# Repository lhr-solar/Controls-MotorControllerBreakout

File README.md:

TODO: update readme for v2.1: added 2 fan connectors, raised TPS2121 current limit & fuse rating

# Controls-MotorControllerBreakout
Author: Ravi Shah  

This Power and CAN interface board for the Prohelion WaveSculptor 22 Motor Controller allows for easier debugging by switching between controls and external power sources and providing a plug-and-play CANdapter interface.  

## BOM
IBOM: BOM/ibom.html (download and view in browser)  
Mouser Cart: https://www.mouser.com/ProjectManager/ProjectDetail.aspx?AccessID=de9c48e362

## Connectors
| # | Name | Type | Ideal Voltage |
| - | - | - | - |
| J1  | MC CAN 1 | Micro-Fit_3.0_43045-0612_2x03_P3.00mm_Vertical Female | +12V |
| J2  | MC CAN 2 | Micro-Fit_3.0_43650-0215_1x02_P3.00mm_Vertical Female | N/A |
| J3  | CTRLS | Micro-Fit_3.0_43045-0612_2x03_P3.00mm_Vertical Female | +12V |
| J4  | EXT PWR | Micro-Fit_3.0_43650-0215_1x02_P3.00mm_Vertical Female | +12V |
| J5  | CANDAPTER | AMPHENOL_L77SDE09SA4CH3R Female | N/A |

## 3D Model

## PCB

## Schematic
### Root

### Power Distribution

### Power Protection

### LEDs

## Application Note
Controls Leader should always be connected to "CTRLS" with the standard CAN+PWR pinout. The motor controller should always be connected to MC CAN 1 and MC CAN 2. To connect external 12V power, the "EXT EN" jumper must be closed. This jumper can be left closed to allow the power muxing IC to choose a source (prioritizing controls), or it can be left open to ignore the external source. In case of a defective IC, the "MNL" jumper can be closed to permanently connect Controls to the output +12V. Otherwise, the "MNL" jumper should be left open.  

+12v is protected by rectifier diodes and fused on both Controls Leader and this board.  

If using a CANdapter for debugging, the "CAN TERM" jumper must be opened. Otherwise, it should be closed, since this board acts as the terminating end for MotorCAN.

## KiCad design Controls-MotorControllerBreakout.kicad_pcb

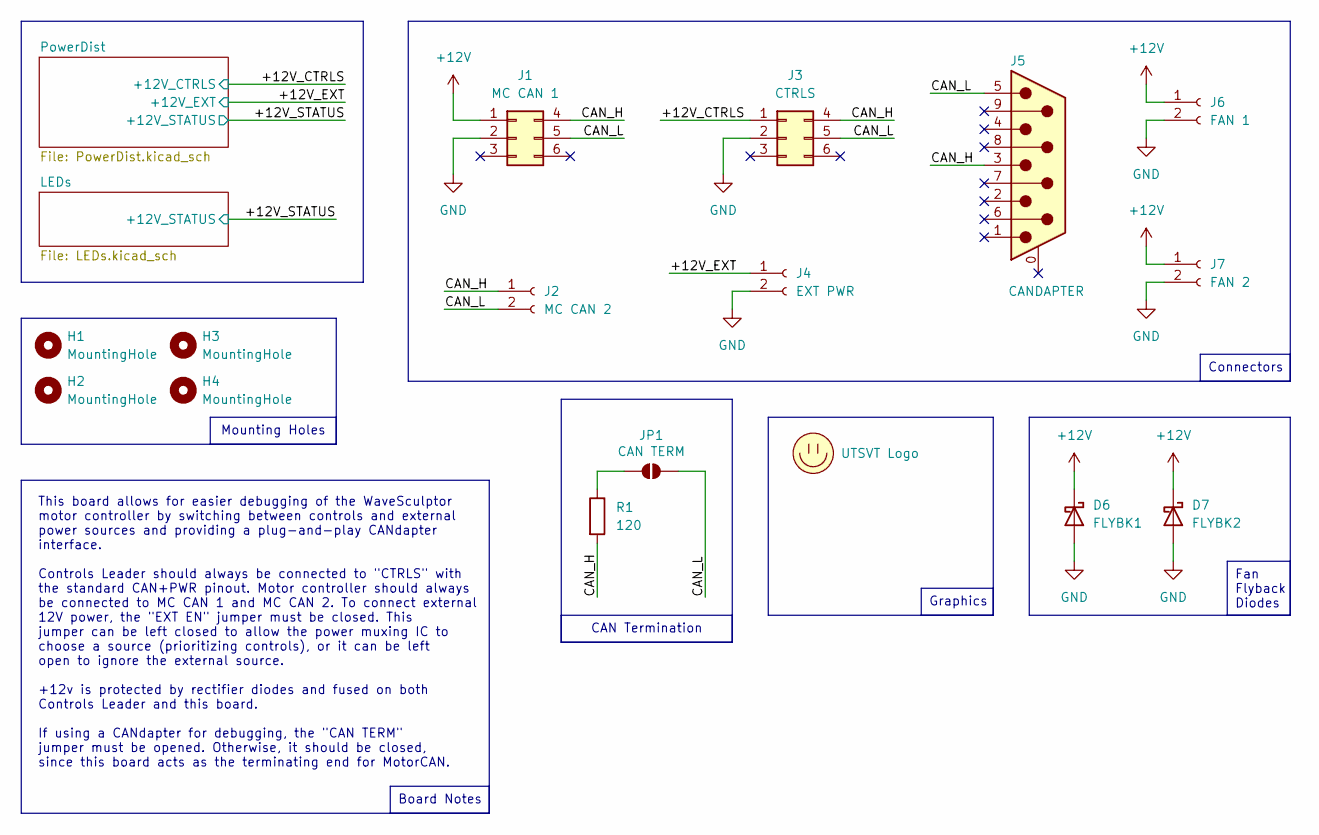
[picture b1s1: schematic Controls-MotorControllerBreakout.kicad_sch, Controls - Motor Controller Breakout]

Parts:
D6: FLYBK1; DO-221AC
D7: FLYBK2; DO-221AC
H1, H2, H3, H4: MountingHole; MountingHole_3mm
J1: MC CAN 1; Molex_Micro-Fit_3.0_43045-0612_2x03_P3.00mm_Vertical
J2: MC CAN 2; Molex_Micro-Fit_3.0_43650-0215_1x02_P3.00mm_Vertical
J3: CTRLS; Molex_Micro-Fit_3.0_43045-0612_2x03_P3.00mm_Vertical
J4: EXT PWR; Molex_Micro-Fit_3.0_43650-0215_1x02_P3.00mm_Vertical
J5: CANDAPTER; AMPHENOL_L77SDE09SA4CH3R
J6: FAN 1; Molex_Micro-Fit_3.0_43650-0215_1x02_P3.00mm_Vertical
J7: FAN 2; Molex_Micro-Fit_3.0_43650-0215_1x02_P3.00mm_Vertical
JP1: CAN TERM; SolderJumper-2_P1.3mm_Open_RoundedPad1.0x1.5mm
LOGO1: UTSVT Logo; UTSVT_Logo_Symbol
R1: 120; R_0805_2012Metric

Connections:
+12V: D6.1 (K), D7.1 (K), J1.1, J6.1, J7.1; also elsewhere on the board
/+12V_CTRLS: J3.1; also elsewhere on the board
/+12V_EXT: J4.1; also elsewhere on the board
/CAN_H: J1.4, J2.1, J3.4, J5.3, R1.2
/CAN_L: J1.5, J2.2, J3.5, J5.5, JP1.2 (B)
GND: D6.2 (A), D7.2 (A), J1.2, J3.2, J4.2, J6.2, J7.2; also elsewhere on the board
unnamed: JP1.1 (A), R1.1

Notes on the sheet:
Graphics
Board Notes
Fan Flyback Diodes
Mounting Holes
Connectors
CAN Termination
This board allows for easier debugging of the WaveSculptor motor controller by switching between controls and external power sources and providing a plug-and-play CANdapter interface. Controls Leader should always be connected to "CTRLS" with the standard CAN+PWR pinout. Motor controller should alw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

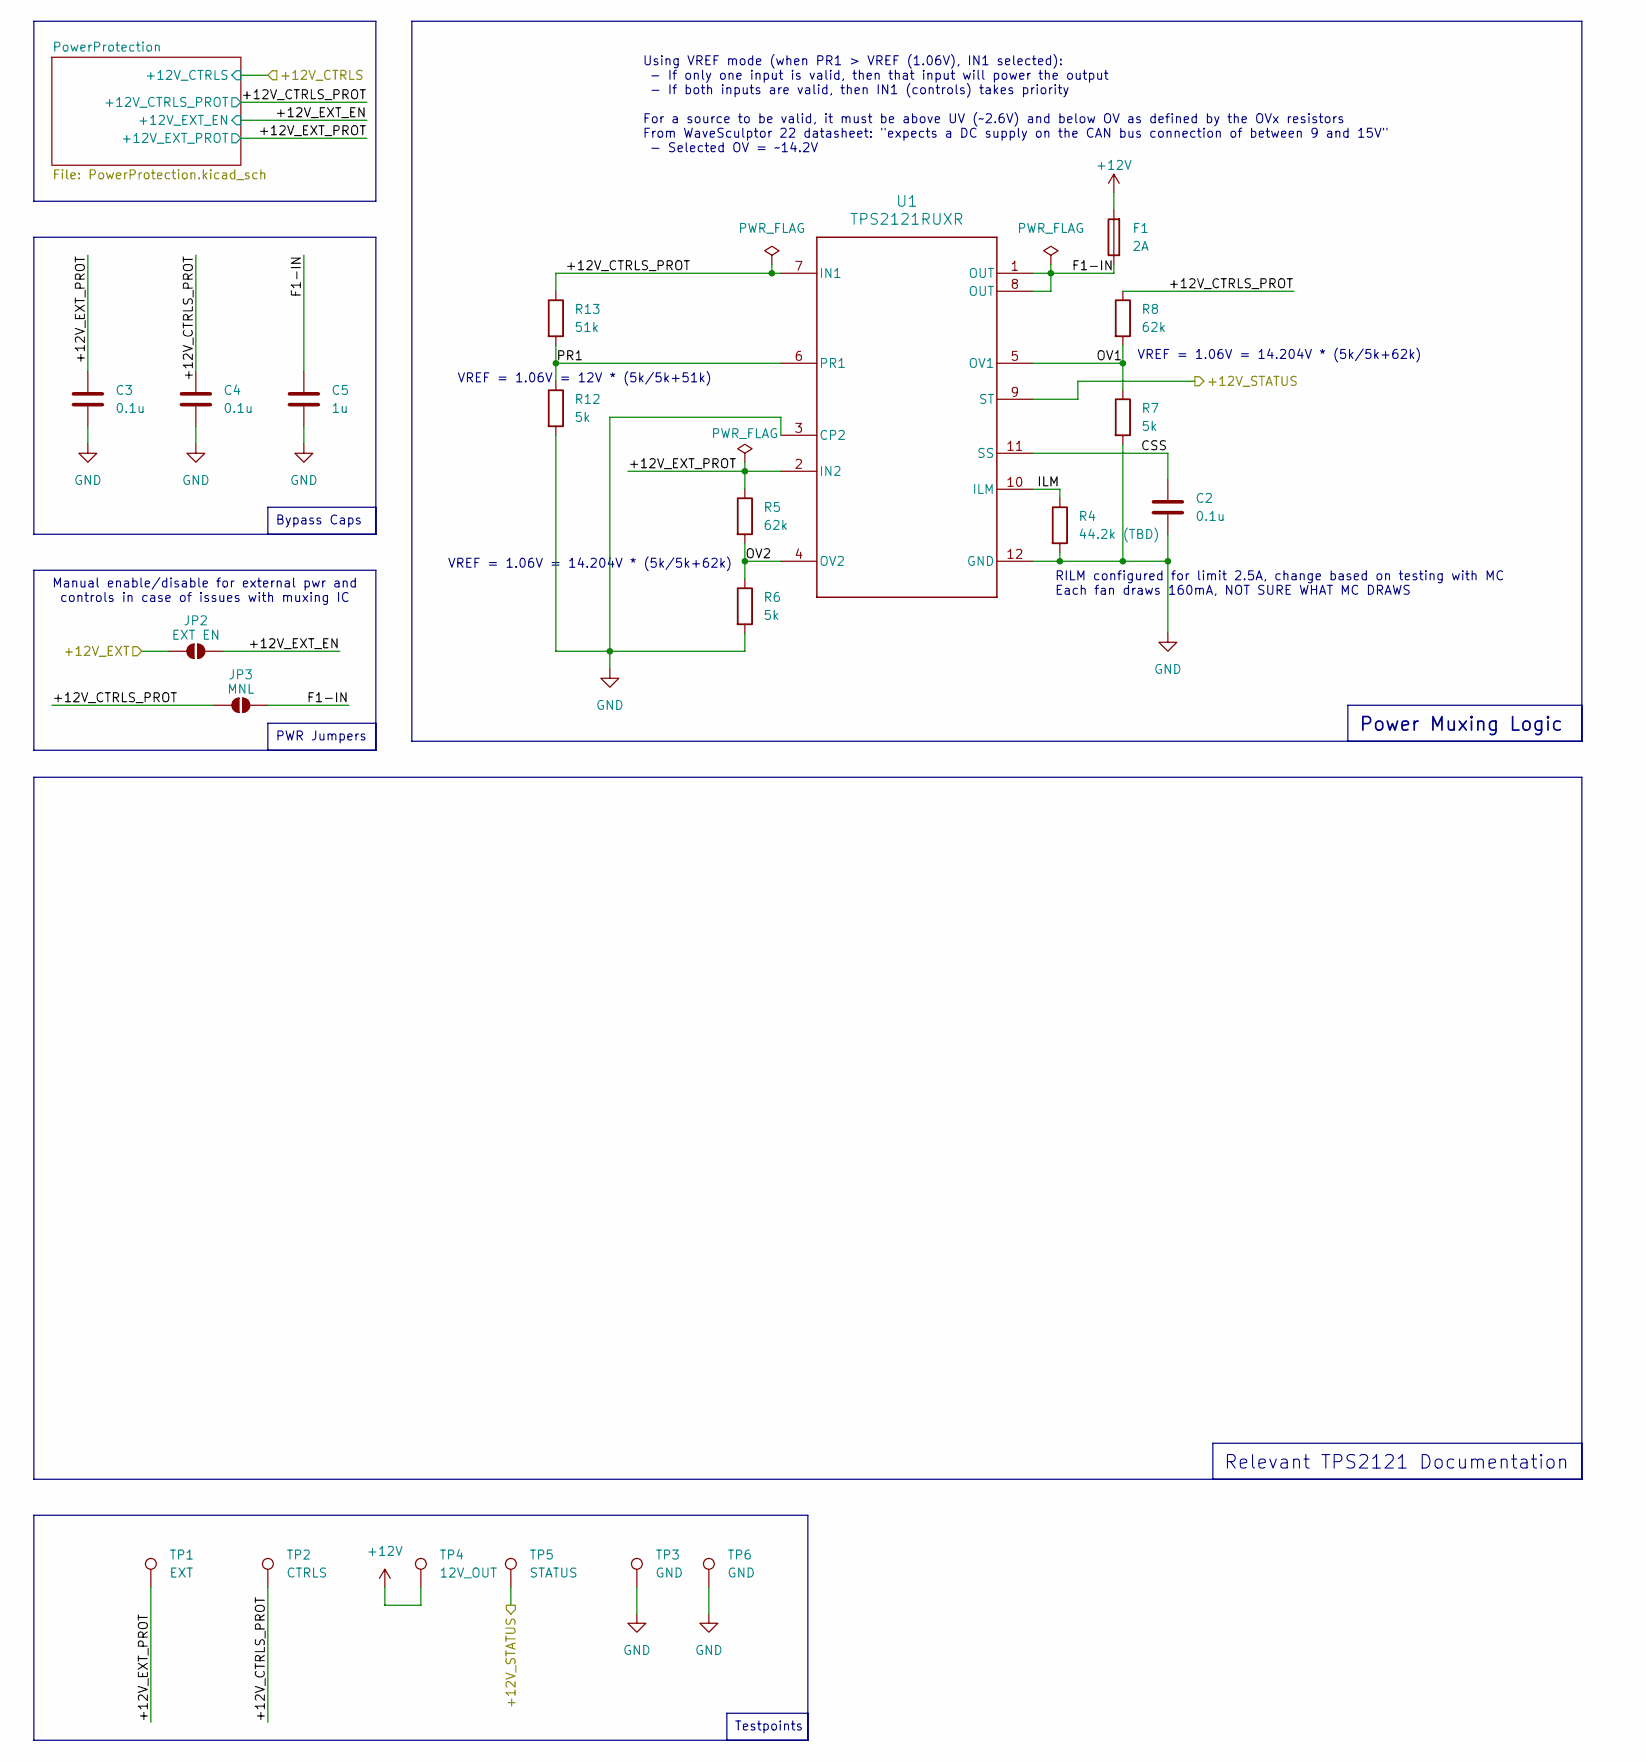
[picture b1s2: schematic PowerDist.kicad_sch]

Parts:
C2, C3, C4: 0.1u; C_0805_2012Metric
C5: 1u; C_0805_2012Metric
F1: 2A; Fuse_1206_3216Metric; Mouser Part Number 576-0440002.WR
JP2: EXT EN; SolderJumper-2_P1.3mm_Open_RoundedPad1.0x1.5mm
JP3: MNL; SolderJumper-2_P1.3mm_Open_RoundedPad1.0x1.5mm
R4: 44.2k (TBD); R_0805_2012Metric
R5, R8: 62k; R_0805_2012Metric
R6, R7, R12: 5k; R_0805_2012Metric
R13: 51k; R_0805_2012Metric
TP1: EXT; TestPoint_Pad_1.0x1.0mm
TP2: CTRLS; TestPoint_Pad_1.0x1.0mm
TP3, TP6: GND; TestPoint_Pad_1.0x1.0mm
TP4: 12V_OUT; TestPoint_Pad_1.0x1.0mm
TP5: STATUS; TestPoint_Pad_1.0x1.0mm
U1: TPS2121RUXR; RUX0012A

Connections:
+12V: F1.2, TP4.1; also elsewhere on the board
/+12V_EXT: JP2.1 (A); also elsewhere on the board
/+12V_STATUS: TP5.1, U1.9 (ST); also elsewhere on the board
/PowerDist/+12V_CTRLS_PROT: C4.1, JP3.1 (A), R8.1, R13.1, TP2.1, U1.7 (IN1); also elsewhere on the board
/PowerDist/+12V_EXT_EN: JP2.2 (B); also elsewhere on the board
/PowerDist/+12V_EXT_PROT: C3.1, R5.1, TP1.1, U1.2 (IN2); also elsewhere on the board
/PowerDist/CSS: C2.1, U1.11 (SS)
/PowerDist/F1-IN: C5.1, F1.1, JP3.2 (B), U1.1 (OUT), U1.8 (OUT)
/PowerDist/ILM: R4.1, U1.10 (ILM)
/PowerDist/OV1: R7.1, R8.2, U1.5 (OV1)
/PowerDist/OV2: R5.2, R6.1, U1.4 (OV2)
/PowerDist/PR1: R12.1, R13.2, U1.6 (PR1)
GND: C2.2, C3.2, C4.2, C5.2, R4.2, R6.2, R7.2, R12.2, TP3.1, TP6.1, U1.3 (CP2), U1.12 (GND); also elsewhere on the board

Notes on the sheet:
Testpoints
Relevant TPS2121 Documentation
PWR Jumpers
Bypass Caps
Power Muxing Logic
VREF = 1.06V = 14.204V * (5k/5k+62k)
VREF = 1.06V = 12V * (5k/5k+51k)
Using VREF mode (when PR1 > VREF (1.06V), IN1 selected): - If only one input is valid, then that input will power the output - If both inputs are valid, then IN1 (controls) takes priority For a source to be valid, it must be above UV (~2.6V) and below OV as defined by the OVx resistors From WaveScu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
RILM configured for limit 2.5A, change based on testing with MC Each fan draws 160mA, NOT SURE WHAT MC DRAWS
Manual enable/disable for external pwr and controls in case of issues with muxing IC

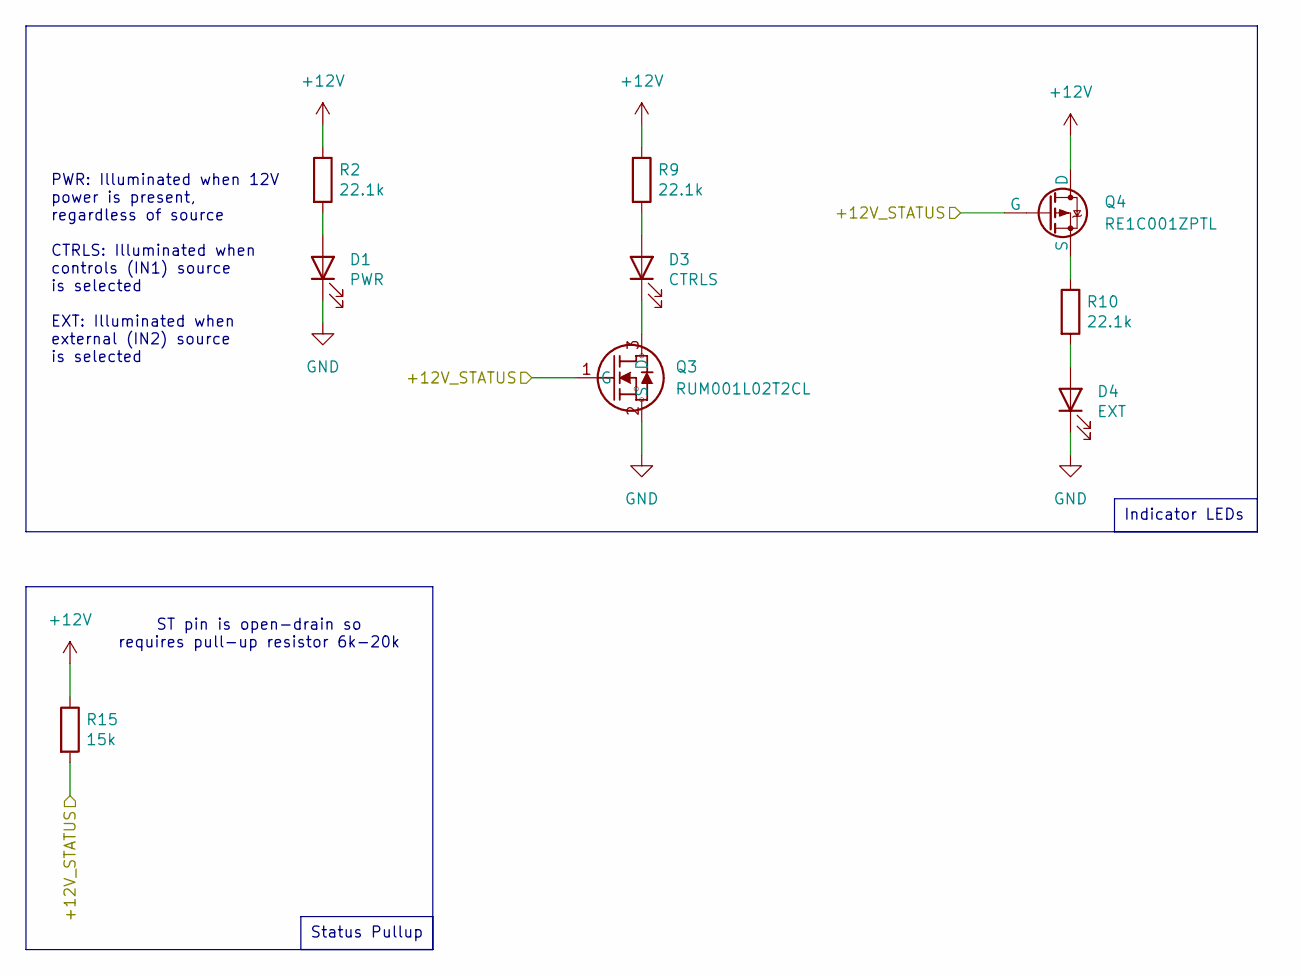
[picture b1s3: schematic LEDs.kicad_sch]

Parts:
D1: PWR; LED_0805_2012Metric; Mouser Part Number 604-APTD2012LCGCK
D3: CTRLS; LED_0805_2012Metric; Mouser Part Number 604-APTD2012LCGCK
D4: EXT; LED_0805_2012Metric; Mouser Part Number 604-APTD2012LCGCK
Q3: RUM001L02T2CL; TRANS_RUM001_ROM
Q4: RE1C001ZPTL; TRANS_RE1C001_ROM
R2, R9, R10: 22.1k; R_0805_2012Metric; Mouser Part Number 71-CRCW0805-22.1K-E3
R15: 15k; R_0805_2012Metric; Mouser Part Number 71-CRCW0805-22.1K-E3

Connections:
+12V: Q4.1 (D), R2.1, R9.1, R15.1; also elsewhere on the board
/+12V_STATUS: Q3.1 (G), Q4.2 (G), R15.2; also elsewhere on the board
GND: D1.1 (K), D4.1 (K), Q3.2 (S); also elsewhere on the board
unnamed: D1.2 (A), R2.2
unnamed: D3.2 (A), R9.2
unnamed: D3.1 (K), Q3.3 (D)
unnamed: D4.2 (A), R10.2
unnamed: Q4.3 (S), R10.1

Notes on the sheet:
Indicator LEDs
Status Pullup
ST pin is open-drain so requires pull-up resistor 6k-20k
PWR: Illuminated when 12V power is present, regardless of source CTRLS: Illuminated when controls (IN1) source is selected EXT: Illuminated when external (IN2) source is selected

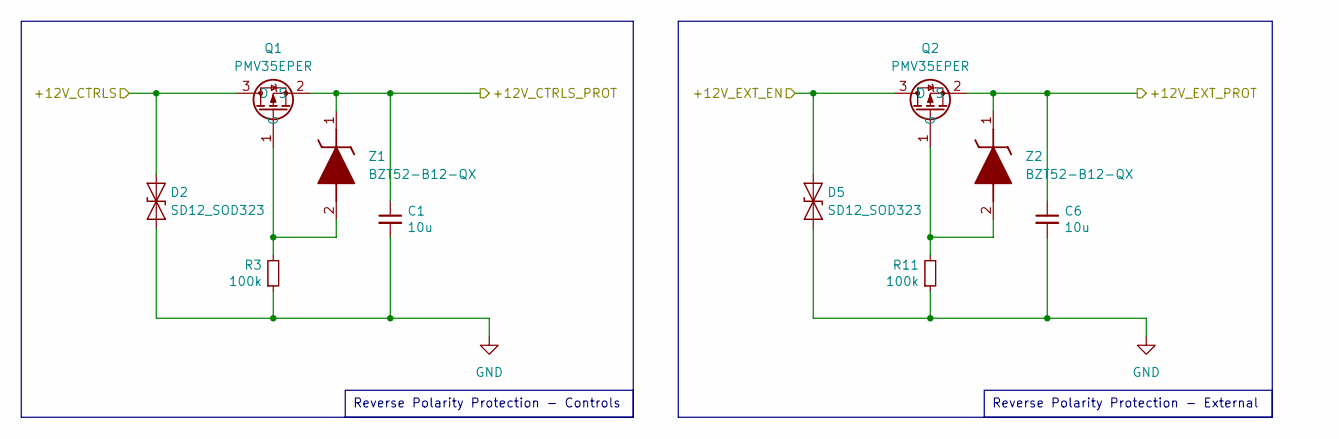
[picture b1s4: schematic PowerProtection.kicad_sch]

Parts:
C1, C6: 10u; C_0805_2012Metric
D2, D5: SD12_SOD323; D_SOD-323
Q1, Q2: PMV35EPER; SOT-23
R3, R11: 100k; R_0805_2012Metric
Z1, Z2: BZT52-B12-QX; BZT52B12QX; Mouser Part Number 771-BZT52-B12-QX

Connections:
/+12V_CTRLS: D2.2 (A2), Q1.3 (D); also elsewhere on the board
/PowerDist/+12V_CTRLS_PROT: C1.1, Q1.2 (S), Z1.1 (K); also elsewhere on the board
/PowerDist/+12V_EXT_EN: D5.2 (A2), Q2.3 (D); also elsewhere on the board
/PowerDist/+12V_EXT_PROT: C6.1, Q2.2 (S), Z2.1 (K); also elsewhere on the board
GND: C1.2, C6.2, D2.1 (A1), D5.1 (A1), R3.1, R11.1; also elsewhere on the board
unnamed: Q1.1 (G), R3.2, Z1.2 (A)
unnamed: Q2.1 (G), R11.2, Z2.2 (A)

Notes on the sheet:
Reverse Polarity Protection - External
Reverse Polarity Protection - Controls

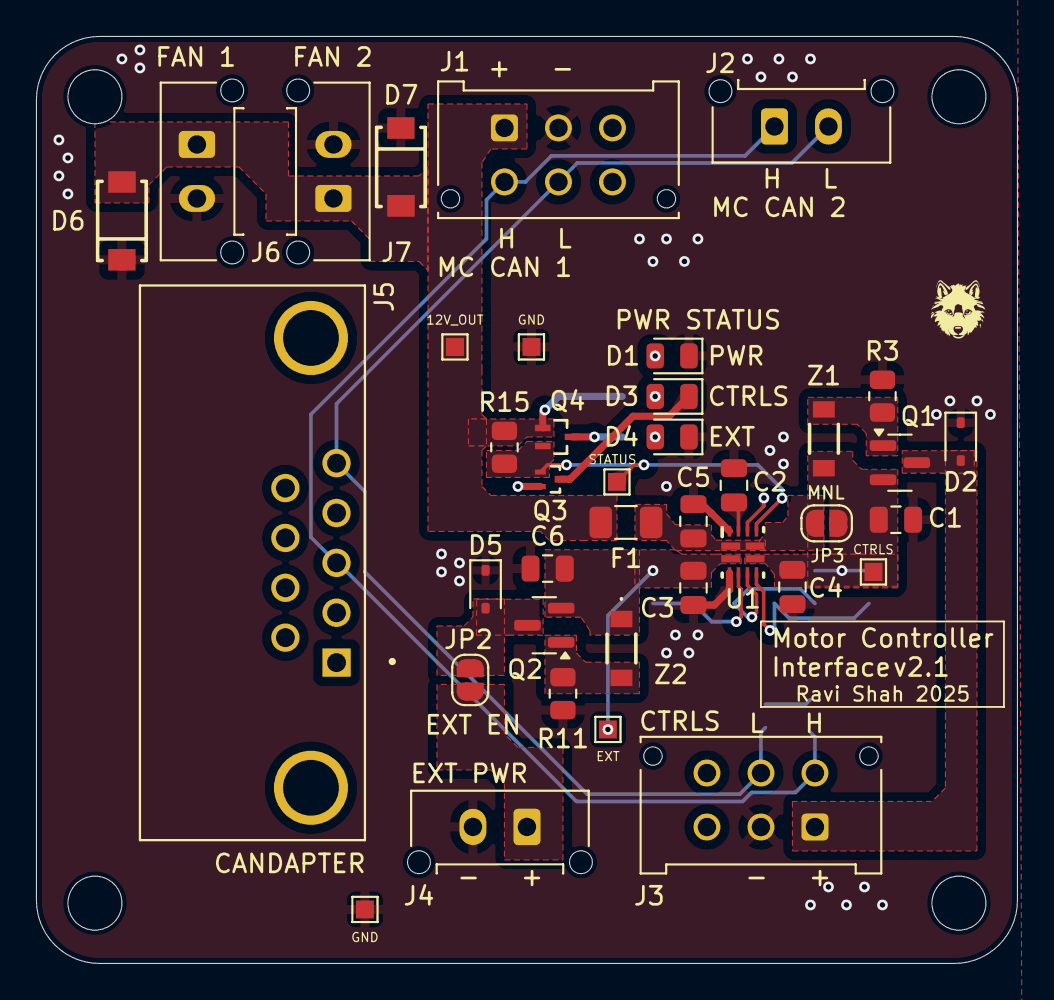
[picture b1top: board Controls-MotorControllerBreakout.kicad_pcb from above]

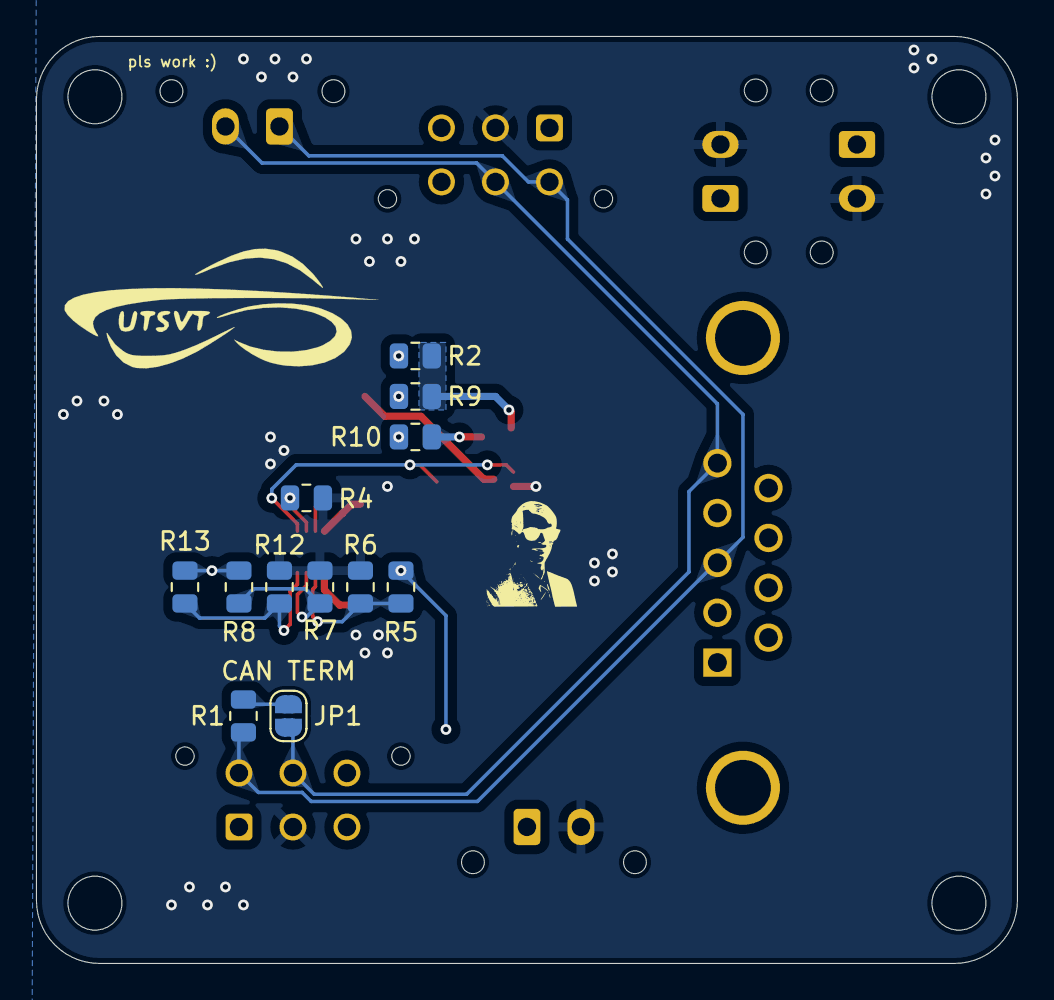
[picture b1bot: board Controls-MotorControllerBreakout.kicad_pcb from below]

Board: 2 copper layers, 54.5 x 51.5 mm, 56 parts (13 on the bottom side), 24 nets.

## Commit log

2024-11-18 add kicad project
2024-11-18 initial sch
2024-11-18 add alternative controls conn
2024-11-18 decouple pwr from can
2024-11-18 pwr led and rm second term resistors
2024-11-19 initial layout/routing
2024-11-19 pr template
2024-11-19 part numbers
2024-11-19 dimensions
2024-11-19 change diode + models
2024-11-19 fix PP & add dsub conn
2024-11-19 rm mountingholes
2024-11-19 gerbs + bom
2024-12-20 planned v2 changes
2024-12-22 separate connector for controls
2024-12-22 sch is sching (tps2121 design)
2024-12-23 cleanup sch and add leds
2024-12-26 layout kinda screwy but it works?
2024-12-26 initial layout
2024-12-30 mc interface footprint & better input pours
2025-01-01 better output/CAN routing + testpoints
2025-01-10 add reverse polarity for both inputs, fixed muxing logic i think
2025-01-10 proper PR1 pullup
2025-01-14 symbol/footprint for RUM001L02T2CL
2025-01-14 LEDs with mosfet
2025-01-14 flip connectors so clip faces inside
2025-01-14 fml aghsjkasjksdhksjjfd
2025-01-14 start layouting again
2025-01-15 new tps2121 layout/zones
2025-01-16 layout redone
2025-01-16 output fuse and solder jumpers
2025-01-16 fix silks
2025-01-16 gerbs
2025-01-16 STEP + gerbs in root
2025-01-16 new mouser cart
2025-01-22 add detailed board description to readme
2025-01-22 add IBOM
2025-01-22 add 3d model, PCB, schematic to readme
2025-01-22 add connectors table to readme
2025-01-22 remove silkscreen comment
2025-01-26 todos for v3.0
2025-03-17 add fan conns, layout + routing
2025-03-17 yuhhh
2025-03-17 read me
2025-03-19 gerbs, BOM
2025-03-23 flyback sch
2025-03-24 hi its me again
